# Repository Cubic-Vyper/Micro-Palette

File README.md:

# Micro-Palette
This device will scan the color of something when the button is pressed, display the name of the color and the color code (rgb), and it will light up an LED under a keyboard switch as the exatct color scaned. I'm making this because it's always so annoying trying to find the color of somthing irl and then use that in inkscape, so I thought this will be a fun chalange to solve that. 

Stasis Page PDF (cuz you would need an account to view the page): https://github.com/Cubic-Vyper/Micro-Palette/blob/f946c92044628488ba2a7e05cdcd6b13fcdf1a42/Stasis_ProjectPage-Micro%20Palette.pdf

Demo Video: [https://youtu.be/u-WEpDEmPeA](https://youtu.be/u-WEpDEmPeA)

 Bill of Materials

| Name | Purpose | Cost Per Item (USD) | Quantity | Total (USD) | Link | Distributor |
|------|---------|---------------------|----------|-------------|------|--------------|
| Custom PCB | this will connect all the parts | $2.10 | 1 | $2.10 | [Link to Listing](https://jlcpcb.com/) | JLCPCB |
| 0.91-inch OLED Display | This will display the color values | $1.99 | 1 | $1.99 | [Link to Listing](https://www.aliexpress.us/item/3256810479037826.html) | Aliexpress |
| TCS34725 Color Sensor | This will detect the color of objects | $3.85 | 1 | $3.85 | [Link to Listing](https://www.aliexpress.us/item/3256807206040384.html) | Aliexpress |
| Seeed Studio XIAO RP2040 | This is the brains of the device | $3.99 | 1 | $3.99 | [Link to Listing](https://www.seeedstudio.com/XIAO-RP2040-v1-0-p-5026.html) | Seed Studio |
| SK6812 MINI-E LEDs | this will display the color | $0.06 | 2 | $0.12 | [Link to Listing](https://www.alibaba.com/product-detail/Reverse-Mount-6028-Rgb-Smd-Led_1600431875998.html) | Alibaba |
| M3 x 12mm Bolts | This will hold everything together | $0.05 | 4 | $0.20 | [Link to Listing](https://www.alibaba.com/product-detail/M1-6-M2-M2-5-M3_1601369820018.html) | Alibaba |
| Keyboard switch | This will control when the scan starts (when pressed) | $0.18 | 1 | $0.18 | [Link to Listing](https://www.alibaba.com/product-detail/Outemu-5-Pin-Silent-Honey-Peach_1601612452658.html) | Alibaba |
| Keycap | This will go on the switch | $0.80 | 1 | $0.80 | [Link to Listing](https://www.alibaba.com/product-detail/Professional-Manufacturer-for-Blank-Abs-Injection_1601714378360.html) | Alibaba |
| 3D Printed Case | This will hold everything | $0.00 | 1 | $0.00 | There isn't a link | I will print this |
| Shipping | |  |  | $5.47 | | |

**Total Cost:** $22.70

here is the Micro Palette fully assembled:

to assemble, first gather all of the parts:

add the assembled pcb to the case:

add the lid and screw it on:

Finally add the keycap:

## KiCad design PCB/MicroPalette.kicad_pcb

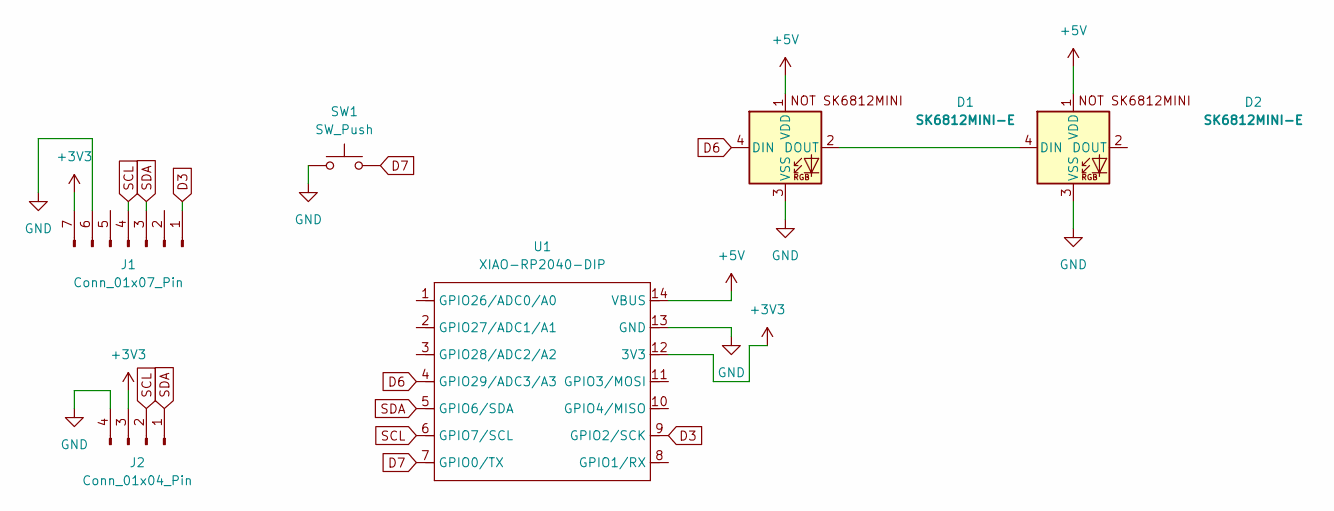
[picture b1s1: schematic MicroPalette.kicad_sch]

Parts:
D1, D2: SK6812MINI-E; SK6812MINI-E_fixed
J1: Conn_01x07_Pin; PinHeader_1x07_P2.54mm_Vertical
J2: Conn_01x04_Pin; PinHeader_1x04_P2.54mm_Vertical
SW1: SW_Push; SW_Cherry_MX_1.00u_PCB
U1: XIAO-RP2040-DIP

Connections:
+3V3: J1.7, J2.3, U1.12 (3V3)
+5V: D1.1 (VDD), D2.1 (VDD), U1.14 (VBUS)
D3: J1.1, U1.9 (GPIO2/SCK)
D6: D1.4 (DIN), U1.4 (GPIO29/ADC3/A3)
D7: SW1.2, U1.7 (GPIO0/TX)
GND: D1.3 (VSS), D2.3 (VSS), J1.6, J2.4, SW1.1, U1.13 (GND)
unnamed: D1.2 (DOUT), D2.4 (DIN)
SCL: J1.4, J2.2, U1.6 (GPIO7/SCL)
SDA: J1.3, J2.1, U1.5 (GPIO6/SDA)

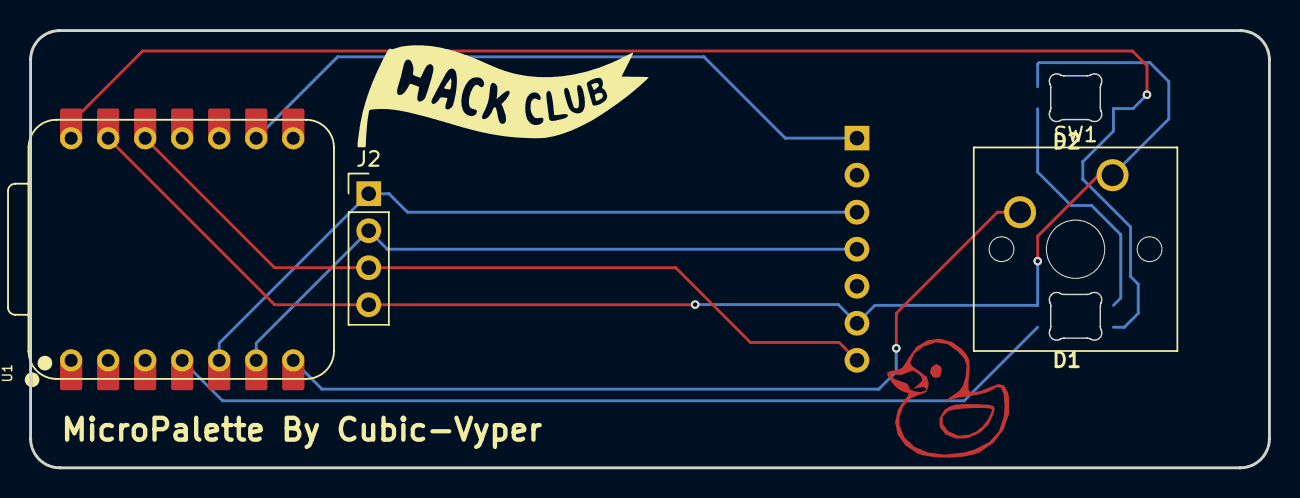
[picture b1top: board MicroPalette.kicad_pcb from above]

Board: 2 copper layers, 85.0 x 30.0 mm, 6 parts (1 on the bottom side), 9 nets.

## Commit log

2026-03-19 Create DELETE
2026-06-25 Add files via upload
    fixed pcb, sda/scl was wrong in the previous version
